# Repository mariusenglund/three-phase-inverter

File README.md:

# 3-phase DC/AC converter with SV-PWM
This repository holds materials of our bachelor's thesis carried out at the Western Norway University of Applied Sciences (HVL), Department of Computer Science, Electrical Engineering and Mathematical Sciences in the spring of 2023.

The thesis can be found at [HVL Open](https://hdl.handle.net/11250/3105460).

> We hope that this report will serve as a valuable resource for those who are interested in the field, and we encourage further development of the provided resources.

## About the Project
The project was aimed at realizing the design and fabrication of a three-phase DC-to-AC converter utilizing the Space Vector Pulse Width Modulation (SV-PWM) algorithm.

<p align="center">
   
   &nbsp; &nbsp; &nbsp; &nbsp;
   
</p>

## Further Work
For suggestions on further work, please refer to the thesis.

## Available Resources
In order to facilitate further advancement, the following resources are made accessible from this repo:

* [PCB design files](pcb-design-files)
* [Source code](source-code)
* [Simulation files](simulation-files)

The repository also contains a [laboratory exercise proposal](/laboratory-exercise/laboratory-exercise-proposal.pdf) that makes use of the inverter. It is worth noting that this exercise is presented in Norwegian.

## License
The resources provided in this repository are released under the GNU General Public License. See the [LICENSE](LICENSE) file for more information.

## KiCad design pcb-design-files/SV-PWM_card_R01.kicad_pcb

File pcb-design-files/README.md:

## PCB Design Files
Download the KiCad project from this location.

***Be aware that the files are still a work in progress.***

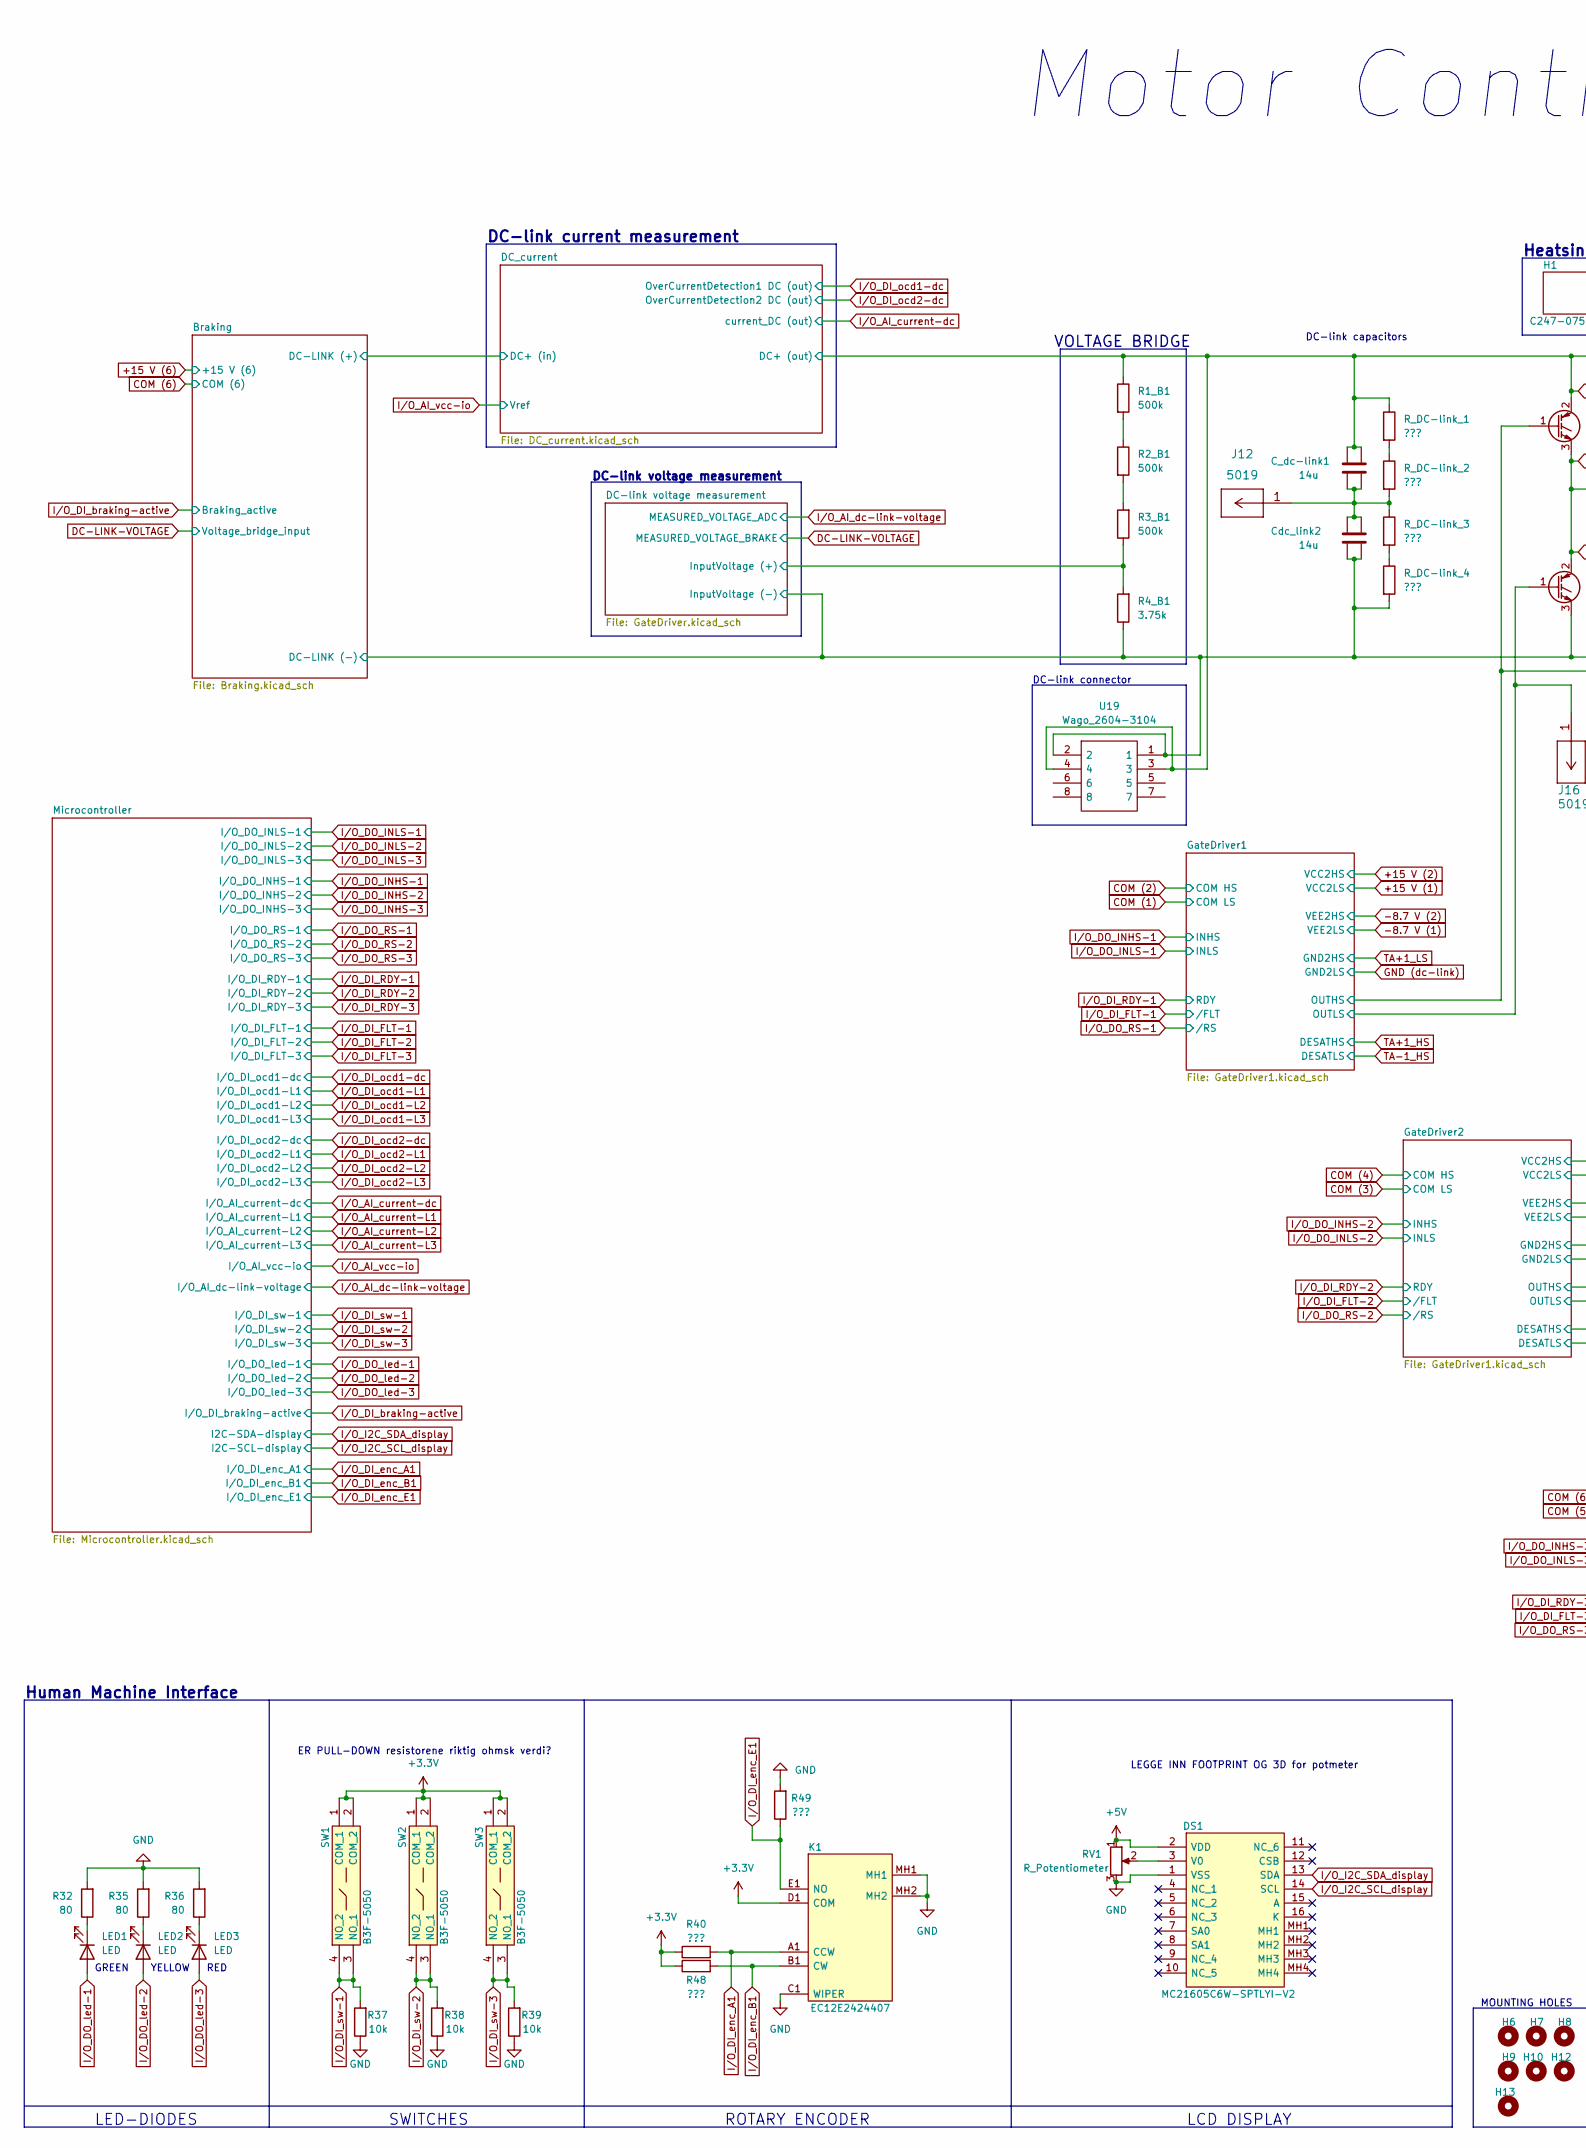
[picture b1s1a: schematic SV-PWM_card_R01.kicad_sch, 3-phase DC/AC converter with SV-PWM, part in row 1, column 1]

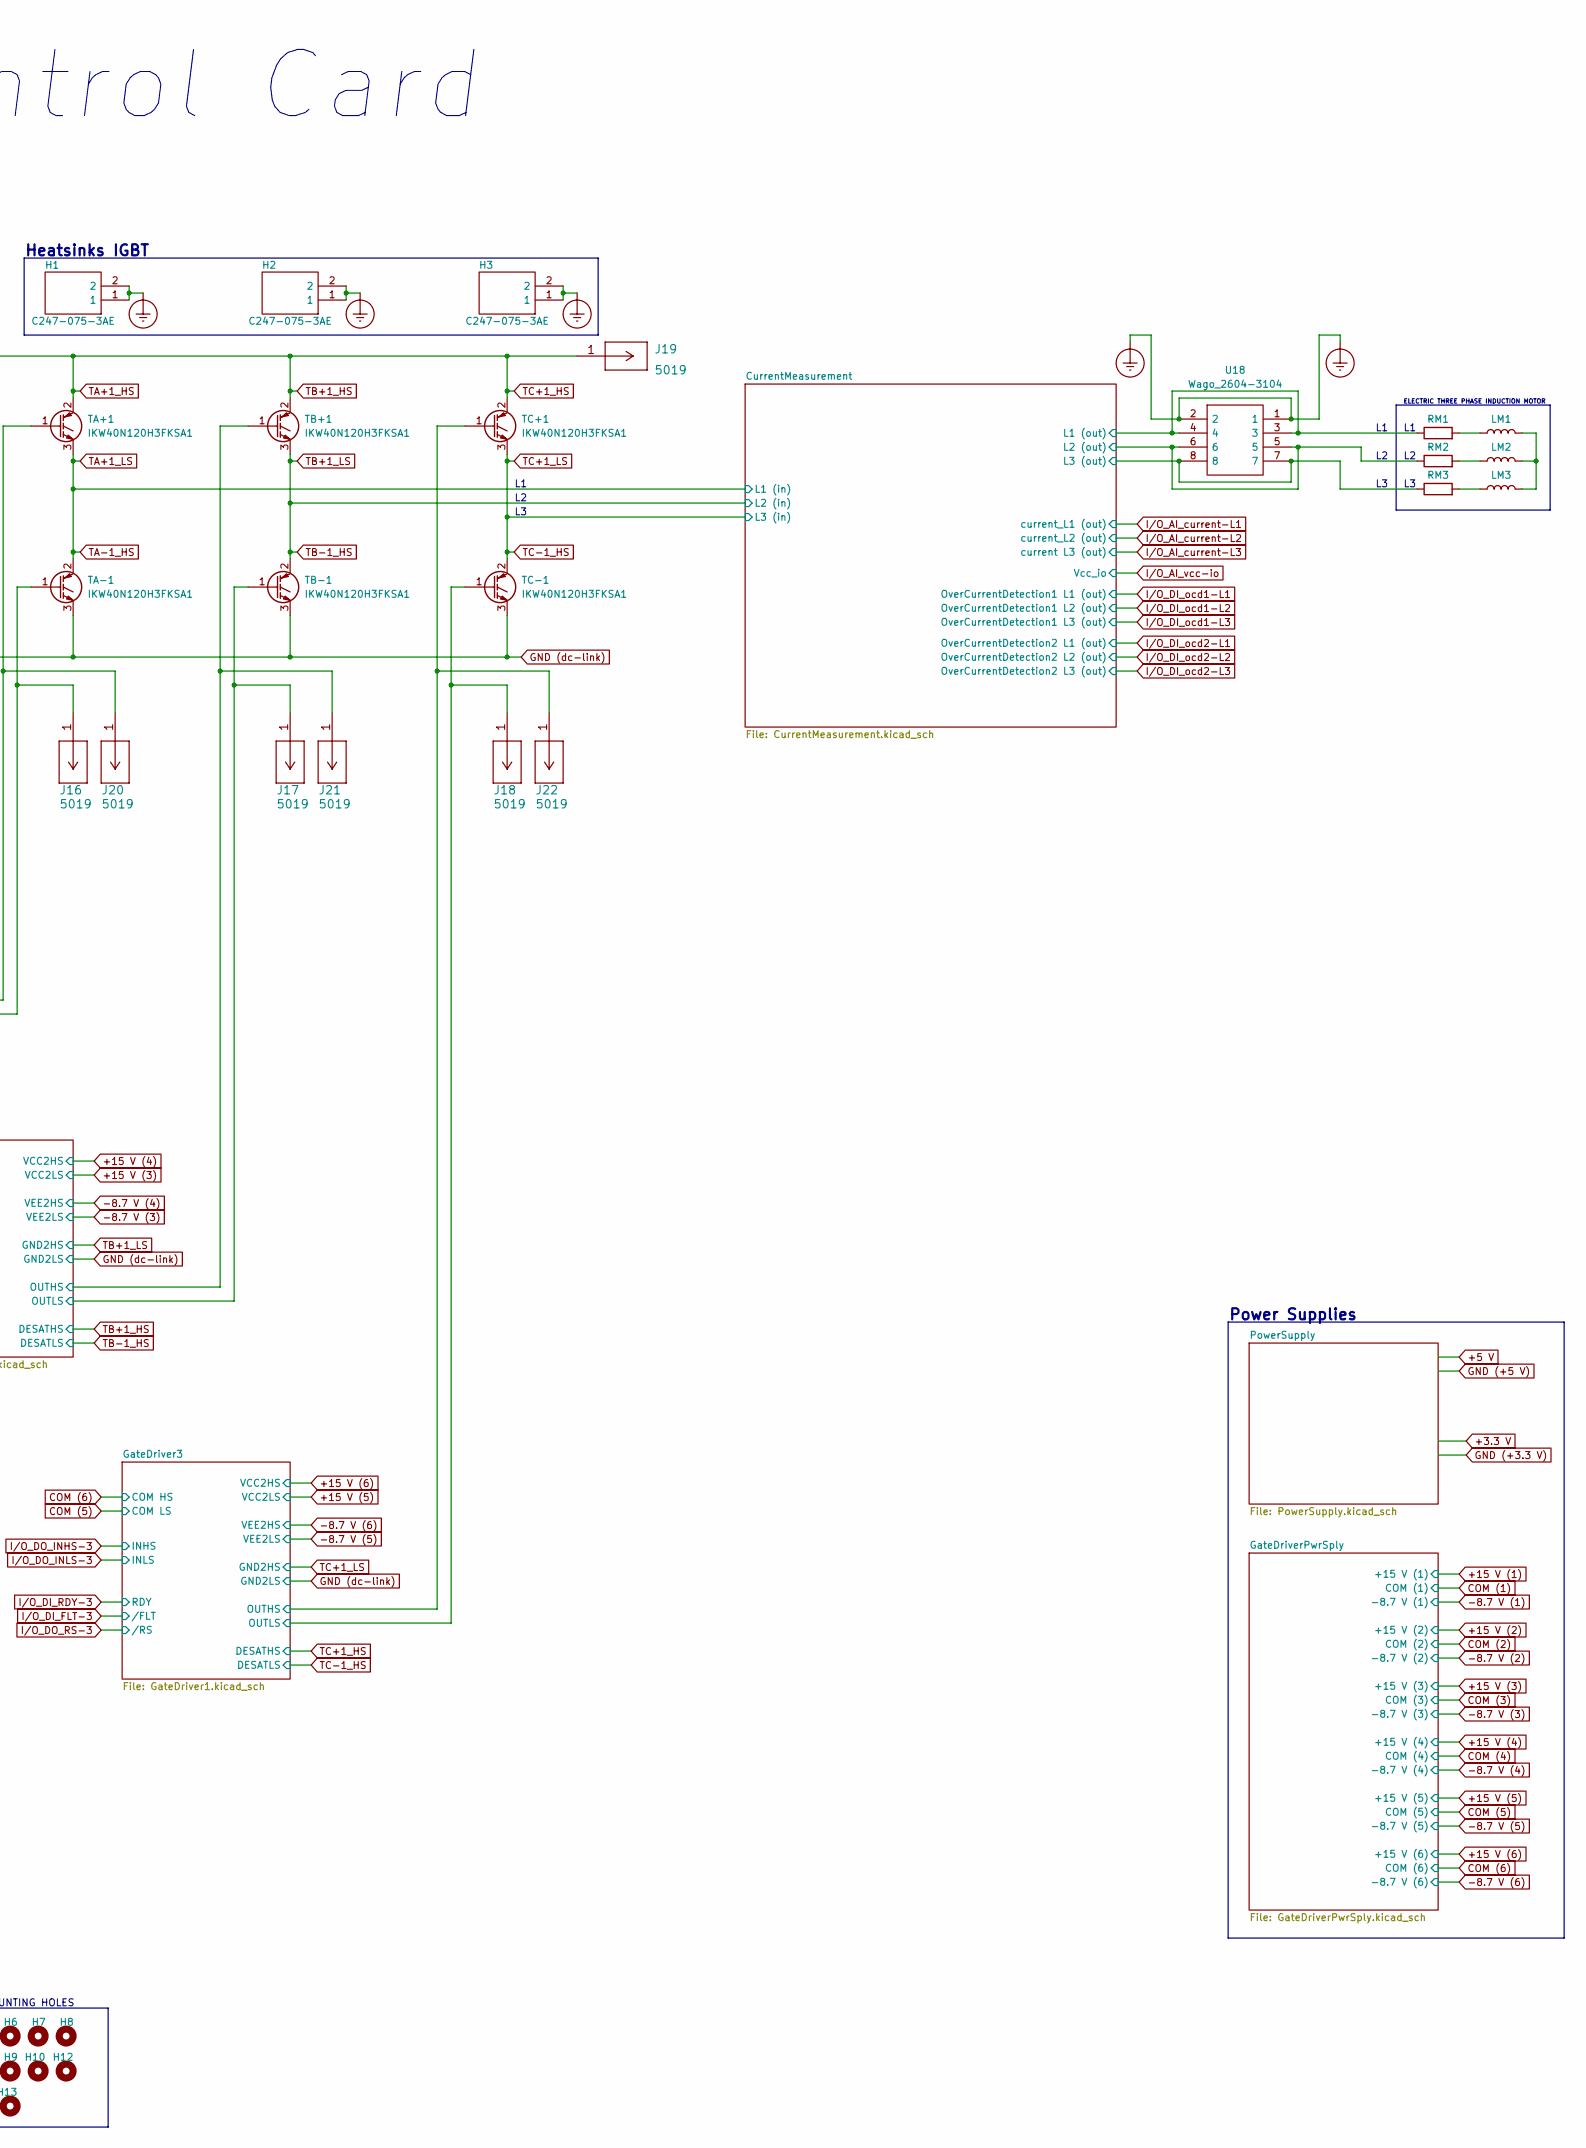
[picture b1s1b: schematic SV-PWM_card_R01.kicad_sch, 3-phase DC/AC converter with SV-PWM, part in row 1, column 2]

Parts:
C_dc-link1: 14u; DC-link-capacitor-B32776G0146K000
Cdc_link2: 14u; DC-link-capacitor-B32776G0146K000
DS1: MC21605C6W-SPTLYI-V2; Display_MC21605C6WSPTLYIV2; Manufacturer_Part_Number MC21605C6W-SPTLYI-V2
H1, H2, H3: C247-075-3AE; Heatsink_C2470753AE; Manufacturer_Part_Number C247-075-3AE; Mouser Part Number 588-C247-075-3AE
H6, H7, H8, H9, H10, H12, H13: MountingHole; MountingHole_4.3mm_M4_DIN965_Pad
J12, J16, J17, J18, J19, J20, J21, J22: 5019; Keystone-5019
K1: EC12E2424407; Encoder_EC12E2424407; Manufacturer_Part_Number EC12E2424407; Mouser Part Number 688-EC12E2424407
LED1: LED; LED_green
LED2: LED; LED_yellow
LED3: LED; LED_red
LM1, LM2, LM3: L
R1_B1, R2_B1, R3_B1: 500k; R_1206_3216Metric_Pad1.30x1.75mm_HandSolder
R4_B1: 3.75k; R_1206_3216Metric_Pad1.30x1.75mm_HandSolder
R32, R35, R36: 80; R_1206_3216Metric_Pad1.30x1.75mm_HandSolder
R37, R38, R39: 10k; R_1206_3216Metric_Pad1.30x1.75mm_HandSolder
R40, R48, R49: ???; R_1206_3216Metric_Pad1.30x1.75mm_HandSolder
RM1, RM2, RM3: R
RV1: R_Potentiometer; Potmeter_3386F1203TLF
R_DC-link_1, R_DC-link_2, R_DC-link_3, R_DC-link_4: ???; R_1206_3216Metric_Pad1.30x1.75mm_HandSolder
SW1, SW2, SW3: B3F-5050; B3F-4055; Manufacturer_Part_Number B3F-5050; Mouser Part Number 653-B3F-5050
TA+1: IKW40N120H3FKSA1; IGBT-TO544P521X1592X2557-3P
TA-1: IKW40N120H3FKSA1; IGBT-TO544P521X1592X2557-3P
TB+1: IKW40N120H3FKSA1; IGBT-TO544P521X1592X2557-3P
TB-1: IKW40N120H3FKSA1; IGBT-TO544P521X1592X2557-3P
TC+1: IKW40N120H3FKSA1; IGBT-TO544P521X1592X2557-3P
TC-1: IKW40N120H3FKSA1; IGBT-TO544P521X1592X2557-3P
U18, U19: Wago_2604-3104; WAGO-26043104; Manufacturer_Part_Number 2604-3104

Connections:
+3.3V: K1.D1 (COM), R40.1, R48.1, SW1.1 (COM_1), SW1.2 (COM_2), SW2.1 (COM_1), SW2.2 (COM_2), SW3.1 (COM_1), SW3.2 (COM_2); also elsewhere on the board
+5V: DS1.2 (VDD), RV1.1; also elsewhere on the board
/CurrentMeasurement/L1 (out): RM1.1, U18.3, U18.4; also elsewhere on the board
/CurrentMeasurement/L2 (out): RM2.1, U18.5, U18.6; also elsewhere on the board
/CurrentMeasurement/L3 (out): RM3.1, U18.7, U18.8; also elsewhere on the board
/GateDriver1/OUTHS: J20.1, TA+1.1 (G); also elsewhere on the board
/GateDriver1/OUTLS: J16.1, TA-1.1 (G); also elsewhere on the board
/GateDriver2/OUTHS: J21.1, TB+1.1 (G); also elsewhere on the board
/GateDriver2/OUTLS: J17.1, TB-1.1 (G); also elsewhere on the board
/GateDriver3/OUTHS: J22.1, TC+1.1 (G); also elsewhere on the board
/GateDriver3/OUTLS: J18.1, TC-1.1 (G); also elsewhere on the board
COM (2): TA+1.3 (E), TA-1.2 (C); also elsewhere on the board
COM (4): TB+1.3 (E), TB-1.2 (C); also elsewhere on the board
COM (6): TC+1.3 (E), TC-1.2 (C); also elsewhere on the board
DC-LINK-VOLTAGE: R3_B1.1, R4_B1.2; also elsewhere on the board
Earth_Protective: H1.1, H1.2, H2.1, H2.2, H3.1, H3.2, U18.1, U18.2; also elsewhere on the board
GND: DS1.1 (VSS), K1.C1 (WIPER), K1.MH1, K1.MH2, R32.2, R35.2, R36.2, R37.1, R38.1, R39.1, R49.2, RV1.3; also elsewhere on the board
GND (dc-link): Cdc_link2.2, Cdc_link2.4, R4_B1.1, R_DC-link_4.2, TA-1.3 (E), TB-1.3 (E), TC-1.3 (E), U19.1, U19.2; also elsewhere on the board
I/O_DI_enc_A1: K1.A1 (CCW), R40.2; also elsewhere on the board
I/O_DI_enc_B1: K1.B1 (CW), R48.2; also elsewhere on the board
I/O_DI_enc_E1: K1.E1 (NO), R49.1; also elsewhere on the board
I/O_DI_sw-1: R37.2, SW1.3 (NO_1), SW1.4 (NO_2); also elsewhere on the board
I/O_DI_sw-2: R38.2, SW2.3 (NO_1), SW2.4 (NO_2); also elsewhere on the board
I/O_DI_sw-3: R39.2, SW3.3 (NO_1), SW3.4 (NO_2); also elsewhere on the board
I/O_DO_led-1: LED1.2 (A); also elsewhere on the board
I/O_DO_led-2: LED2.2 (A); also elsewhere on the board
I/O_DO_led-3: LED3.2 (A); also elsewhere on the board
I/O_I2C_SCL_display: DS1.14 (SCL); also elsewhere on the board
I/O_I2C_SDA_display: DS1.13 (SDA); also elsewhere on the board
unnamed: C_dc-link1.2, C_dc-link1.4, Cdc_link2.1, Cdc_link2.3, J12.1, R_DC-link_2.2, R_DC-link_3.1
unnamed: DS1.3 (V0), RV1.2
unnamed: LED1.1 (K), R32.1
unnamed: LED2.1 (K), R35.1
unnamed: LED3.1 (K), R36.1
unnamed: LM1.1, RM1.2
unnamed: LM1.2, LM2.2, LM3.2
unnamed: LM2.1, RM2.2
unnamed: LM3.1, RM3.2
unnamed: R1_B1.2, R2_B1.1
unnamed: R2_B1.2, R3_B1.2
unnamed: R_DC-link_1.2, R_DC-link_2.1
unnamed: R_DC-link_3.2, R_DC-link_4.1
TA+1_HS: C_dc-link1.1, C_dc-link1.3, J19.1, R1_B1.1, R_DC-link_1.1, TA+1.2 (C), TB+1.2 (C), TC+1.2 (C), U19.3, U19.4; also elsewhere on the board

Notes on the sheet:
DC-link capacitors
DC-link connector
DC-link current measurement
LCD DISPLAY
LEGGE INN FOOTPRINT OG 3D for potmeter
LED-DIODES
DC-link voltage measurement
Power Supplies
RED
GREEN
Heatsinks IGBT
ER PULL-DOWN resistorene riktig ohmsk verdi?
ROTARY ENCODER
YELLOW
MOUNTING HOLES
SWITCHES
Motor Control Card
VOLTAGE BRIDGE
ELECTRIC THREE PHASE INDUCTION MOTOR
Human Machine Interface

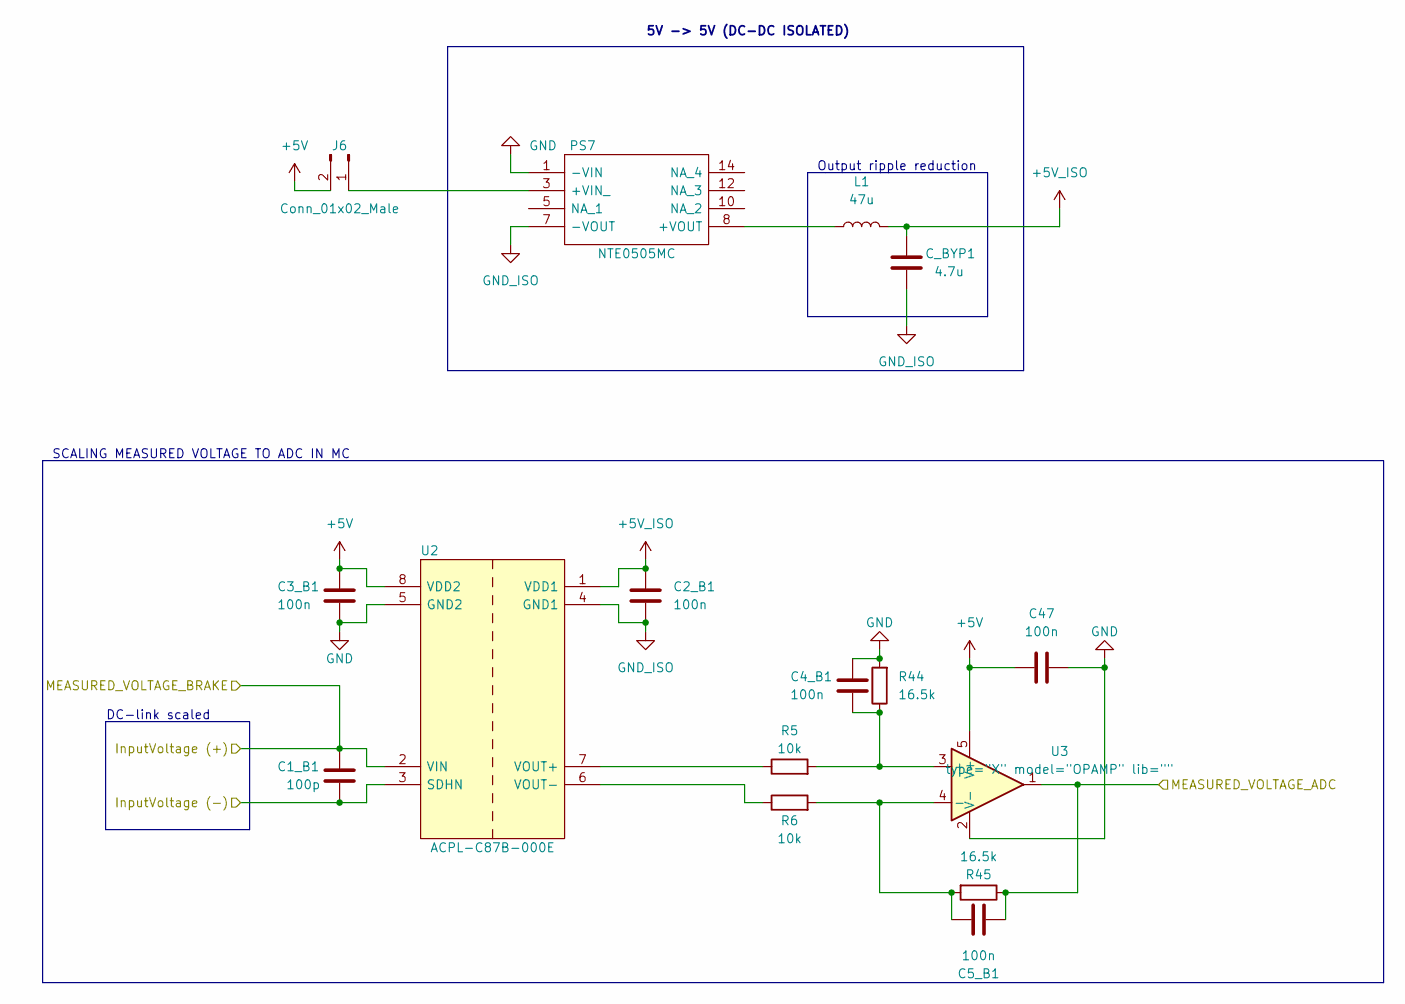
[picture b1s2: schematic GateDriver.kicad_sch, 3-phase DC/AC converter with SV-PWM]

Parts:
C1_B1: 100p; C_1206_3216Metric_Pad1.33x1.80mm_HandSolder
C2_B1, C3_B1, C4_B1, C5_B1, C47: 100n; C_1206_3216Metric_Pad1.33x1.80mm_HandSolder
C_BYP1: 4.7u; C_1206_3216Metric_Pad1.33x1.80mm_HandSolder
J6: Conn_01x02_Male; PinHeader_1x02_P1.00mm_Vertical
L1: 47u; L_2010_5025Metric_Pad1.52x2.65mm_HandSolder
PS7: NTE0505MC; DC-DC-NTE0505MC; Manufacturer_Part_Number NTE0505MC; Mouser Part Number 580-NTE0505MC
R5, R6: 10k; R_1206_3216Metric_Pad1.30x1.75mm_HandSolder
R44, R45: 16.5k; R_1206_3216Metric_Pad1.30x1.75mm_HandSolder
U2: ACPL-C87B-000E; ACPL-SOIC127P1150X331-8N; Manufacturer_Part_Number ACPL-C87B-000E; Mouser Part Number 630-ACPL-C87B-000E
U3: type="X" model="OPAMP" lib=""; OPA237-SOT95P280X145-5N

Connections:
+5V: C3_B1.1, C47.1, J6.2, U2.8 (VDD2), U3.5 (V+); also elsewhere on the board
+5V_ISO: C2_B1.1, C_BYP1.1, L1.2, U2.1 (VDD1)
DC-LINK-VOLTAGE: C1_B1.1, U2.2 (VIN); also elsewhere on the board
GND: C3_B1.2, C4_B1.2, C47.2, PS7.1 (-VIN), R44.2, U2.5 (GND2), U3.2 (V-); also elsewhere on the board
GND (dc-link): C1_B1.2, U2.3 (SDHN); also elsewhere on the board
GND_ISO: C2_B1.2, C_BYP1.2, PS7.7 (-VOUT), U2.4 (GND1)
I/O_AI_dc-link-voltage: C5_B1.1, R45.1, U3.1; also elsewhere on the board
unnamed: C4_B1.1, R5.2, R44.1, U3.3 (+)
unnamed: C5_B1.2, R6.2, R45.2, U3.4 (-)
unnamed: J6.1, PS7.3 (+VIN_)
unnamed: L1.1, PS7.8 (+VOUT)
unnamed: R5.1, U2.7 (VOUT+)
unnamed: R6.1, U2.6 (VOUT-)

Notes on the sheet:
DC-link scaled
Output ripple reduction
SCALING MEASURED VOLTAGE TO ADC IN MC
5V -> 5V (DC-DC ISOLATED)

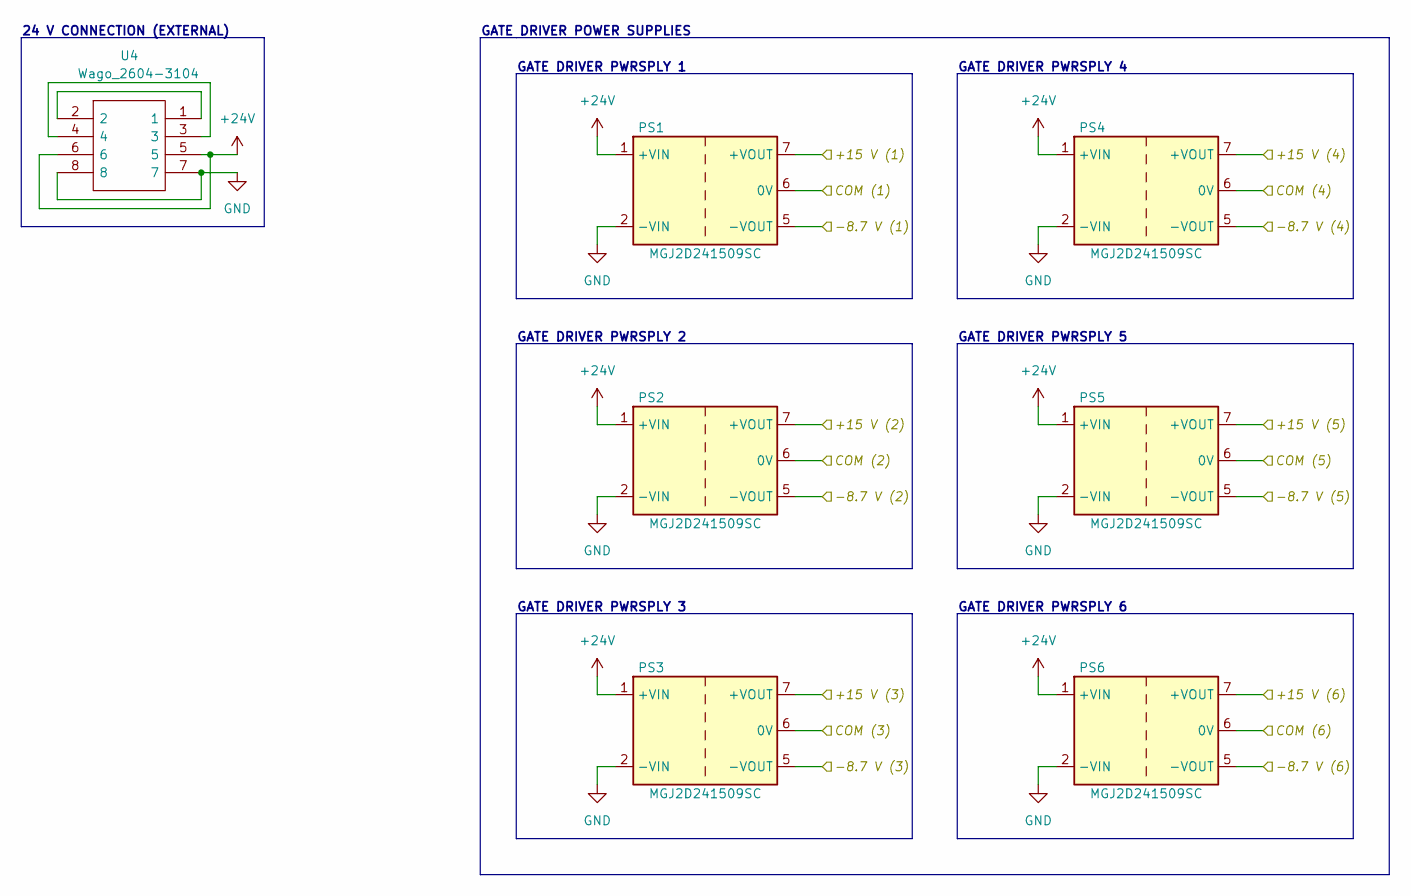
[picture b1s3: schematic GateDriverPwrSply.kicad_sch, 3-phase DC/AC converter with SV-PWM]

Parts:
PS1, PS2, PS3, PS4, PS5, PS6: MGJ2D241509SC; Converter_DCDC_Murata_MGJ2DxxxxxxSC_THT
U4: Wago_2604-3104; WAGO-26043104; Manufacturer_Part_Number 2604-3104

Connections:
+15 V (1): PS1.7 (+VOUT); also elsewhere on the board
+15 V (2): PS2.7 (+VOUT); also elsewhere on the board
+15 V (3): PS3.7 (+VOUT); also elsewhere on the board
+15 V (4): PS4.7 (+VOUT); also elsewhere on the board
+15 V (5): PS5.7 (+VOUT); also elsewhere on the board
+15 V (6): PS6.7 (+VOUT); also elsewhere on the board
+24V: PS1.1 (+VIN), PS2.1 (+VIN), PS3.1 (+VIN), PS4.1 (+VIN), PS5.1 (+VIN), PS6.1 (+VIN), U4.5, U4.6; also elsewhere on the board
-8.7 V (1): PS1.5 (-VOUT); also elsewhere on the board
-8.7 V (2): PS2.5 (-VOUT); also elsewhere on the board
-8.7 V (3): PS3.5 (-VOUT); also elsewhere on the board
-8.7 V (4): PS4.5 (-VOUT); also elsewhere on the board
-8.7 V (5): PS5.5 (-VOUT); also elsewhere on the board
-8.7 V (6): PS6.5 (-VOUT); also elsewhere on the board
COM (2): PS2.6 (0V); also elsewhere on the board
COM (4): PS4.6 (0V); also elsewhere on the board
COM (6): PS6.6 (0V); also elsewhere on the board
GND: PS1.2 (-VIN), PS2.2 (-VIN), PS3.2 (-VIN), PS4.2 (-VIN), PS5.2 (-VIN), PS6.2 (-VIN), U4.7, U4.8; also elsewhere on the board
GND (dc-link): PS1.6 (0V), PS3.6 (0V), PS5.6 (0V); also elsewhere on the board
unnamed: U4.1, U4.2
unnamed: U4.3, U4.4

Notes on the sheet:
GATE DRIVER PWRSPLY 6
GATE DRIVER PWRSPLY 5
GATE DRIVER POWER SUPPLIES
GATE DRIVER PWRSPLY 4
GATE DRIVER PWRSPLY 2
24 V CONNECTION (EXTERNAL)
GATE DRIVER PWRSPLY 3
GATE DRIVER PWRSPLY 1

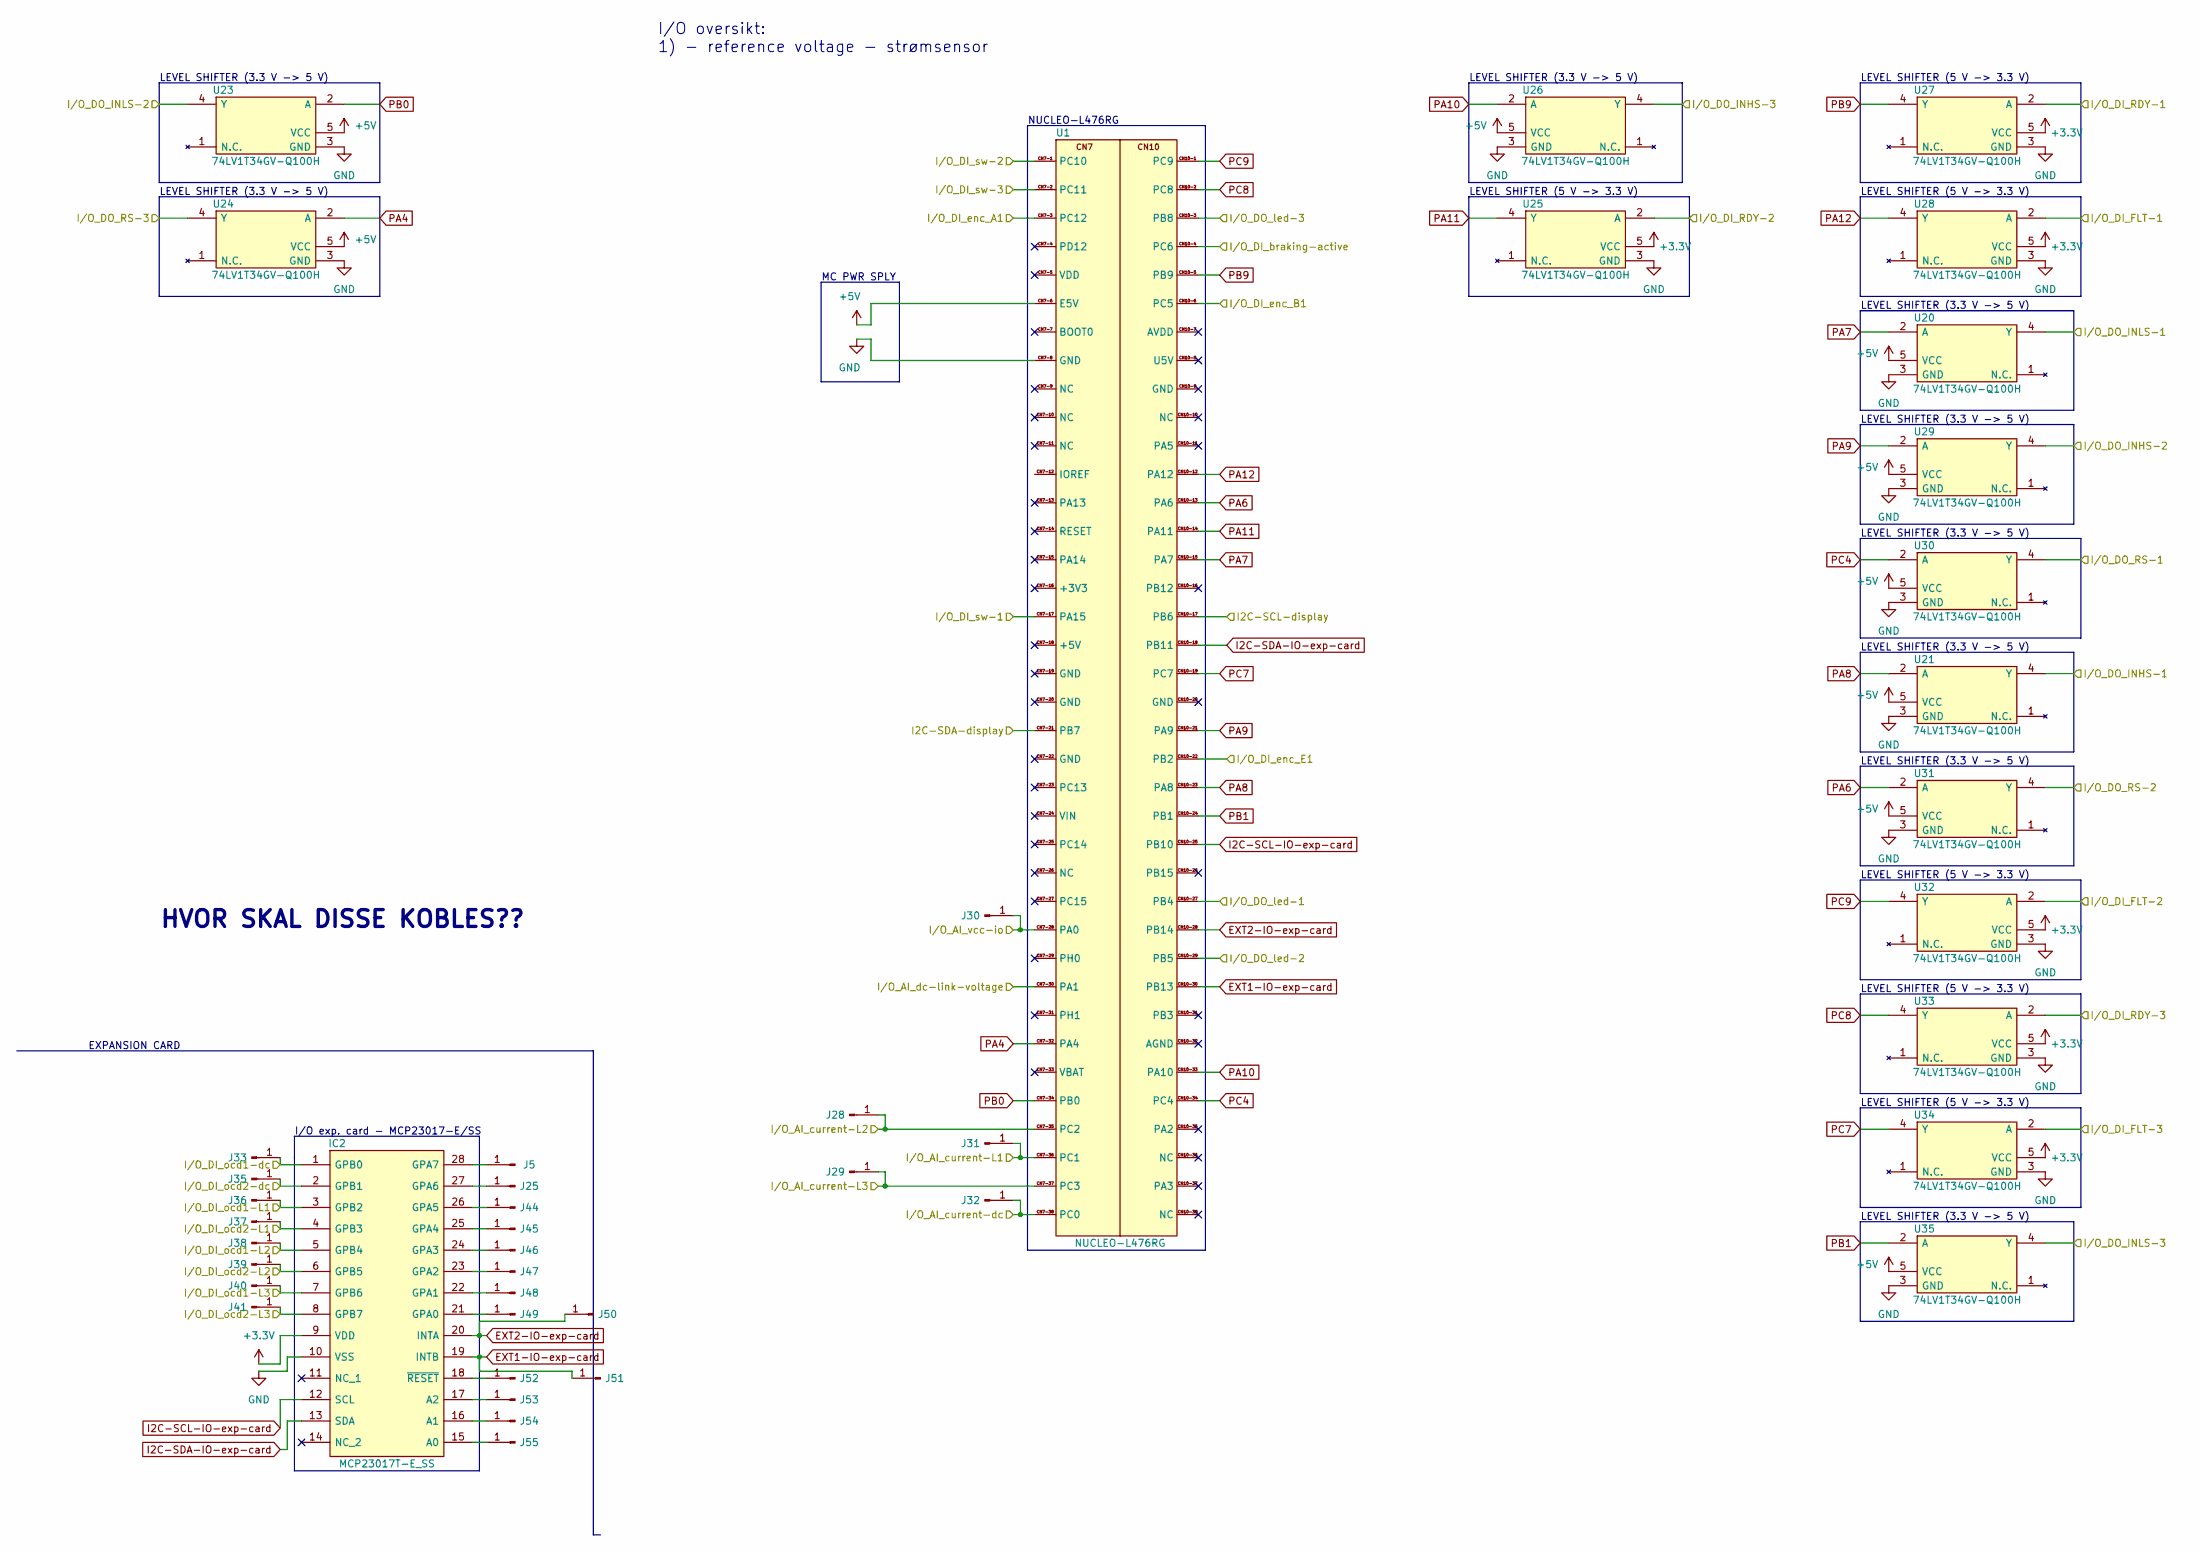
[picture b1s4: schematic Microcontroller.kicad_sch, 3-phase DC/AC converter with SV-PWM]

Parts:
IC2: MCP23017T-E_SS; MCP23017T-ESS-SOP65P780X200-28N; Manufacturer_Part_Number MCP23017T-E/SS; Mouser Part Number 579-MCP23017T-E/SS
J5, J25, J28, J29, J30, J31, J32, J33, J35, J36, J37, J38, J39, J40, J41, J44, J45, J46, J47, J48, J49, J50, J51, J52, J53, J54, J55: Conn_01x01_Male; PinHeader_1x01_P1.00mm_Vertical
U1: NUCLEO-L476RG; PCB-receptable Nucleo-L476RG
U20, U21, U23, U24, U25, U26, U27, U28, U29, U30, U31, U32, U33, U34, U35: 74LV1T34GV-Q100H; nexperia-SOT95P275X110-5N; Manufacturer_Part_Number 74LV1T34GV-Q100H; Mouser Part Number 771-74LV1T34GV-Q100H

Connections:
+3.3V: IC2.9 (VDD), U25.5 (VCC), U27.5 (VCC), U28.5 (VCC), U32.5 (VCC), U33.5 (VCC), U34.5 (VCC); also elsewhere on the board
+5V: U1.CN7-6 (E5V), U20.5 (VCC), U21.5 (VCC), U23.5 (VCC), U24.5 (VCC), U26.5 (VCC), U29.5 (VCC), U30.5 (VCC), U31.5 (VCC), U35.5 (VCC); also elsewhere on the board
EXT1-IO-exp-card: IC2.19 (INTB), J51.1, U1.CN10-30 (PB13)
EXT2-IO-exp-card: IC2.20 (INTA), J50.1, U1.CN10-28 (PB14)
GND: IC2.10 (VSS), U1.CN7-8 (GND), U20.3 (GND), U21.3 (GND), U23.3 (GND), U24.3 (GND), U25.3 (GND), U26.3 (GND), U27.3 (GND), U28.3 (GND), U29.3 (GND), U30.3 (GND), U31.3 (GND), U32.3 (GND), U33.3 (GND), U34.3 (GND), U35.3 (GND); also elsewhere on the board
I2C-SCL-IO-exp-card: IC2.12 (SCL), U1.CN10-25 (PB10)
I2C-SDA-IO-exp-card: IC2.13 (SDA), U1.CN10-18 (PB11)
I/O_AI_current-L1: J31.1, U1.CN7-36 (PC1); also elsewhere on the board
I/O_AI_current-L2: J28.1, U1.CN7-35 (PC2); also elsewhere on the board
I/O_AI_current-L3: J29.1, U1.CN7-37 (PC3); also elsewhere on the board
I/O_AI_current-dc: J32.1, U1.CN7-38 (PC0); also elsewhere on the board
I/O_AI_dc-link-voltage: U1.CN7-30 (PA1); also elsewhere on the board
I/O_AI_vcc-io: J30.1, U1.CN7-28 (PA0); also elsewhere on the board
I/O_DI_FLT-1: U28.2 (A); also elsewhere on the board
I/O_DI_FLT-2: U32.2 (A); also elsewhere on the board
I/O_DI_FLT-3: U34.2 (A); also elsewhere on the board
I/O_DI_RDY-1: U27.2 (A); also elsewhere on the board
I/O_DI_RDY-2: U25.2 (A); also elsewhere on the board
I/O_DI_RDY-3: U33.2 (A); also elsewhere on the board
I/O_DI_braking-active: U1.CN10-4 (PC6); also elsewhere on the board
I/O_DI_enc_A1: U1.CN7-3 (PC12); also elsewhere on the board
I/O_DI_enc_B1: U1.CN10-6 (PC5); also elsewhere on the board
I/O_DI_enc_E1: U1.CN10-22 (PB2); also elsewhere on the board
I/O_DI_ocd1-L1: IC2.3 (GPB2), J36.1; also elsewhere on the board
I/O_DI_ocd1-L2: IC2.5 (GPB4), J38.1; also elsewhere on the board
I/O_DI_ocd1-L3: IC2.7 (GPB6), J40.1; also elsewhere on the board
I/O_DI_ocd1-dc: IC2.1 (GPB0), J33.1; also elsewhere on the board
I/O_DI_ocd2-L1: IC2.4 (GPB3), J37.1; also elsewhere on the board
I/O_DI_ocd2-L2: IC2.6 (GPB5), J39.1; also elsewhere on the board
I/O_DI_ocd2-L3: IC2.8 (GPB7), J41.1; also elsewhere on the board
I/O_DI_ocd2-dc: IC2.2 (GPB1), J35.1; also elsewhere on the board
I/O_DI_sw-1: U1.CN7-17 (PA15); also elsewhere on the board
I/O_DI_sw-2: U1.CN7-1 (PC10); also elsewhere on the board
I/O_DI_sw-3: U1.CN7-2 (PC11); also elsewhere on the board
I/O_DO_INHS-1: U21.4 (Y); also elsewhere on the board
I/O_DO_INHS-2: U29.4 (Y); also elsewhere on the board
I/O_DO_INHS-3: U26.4 (Y); also elsewhere on the board
I/O_DO_INLS-1: U20.4 (Y); also elsewhere on the board
I/O_DO_INLS-2: U23.4 (Y); also elsewhere on the board
I/O_DO_INLS-3: U35.4 (Y); also elsewhere on the board
I/O_DO_RS-1: U30.4 (Y); also elsewhere on the board
I/O_DO_RS-2: U31.4 (Y); also elsewhere on the board
I/O_DO_RS-3: U24.4 (Y); also elsewhere on the board
I/O_DO_led-1: U1.CN10-27 (PB4); also elsewhere on the board
I/O_DO_led-2: U1.CN10-29 (PB5); also elsewhere on the board
I/O_DO_led-3: U1.CN10-3 (PB8); also elsewhere on the board
I/O_I2C_SCL_display: U1.CN10-17 (PB6); also elsewhere on the board
I/O_I2C_SDA_display: U1.CN7-21 (PB7); also elsewhere on the board
unnamed: IC2.15 (A0), J55.1
unnamed: IC2.16 (A1), J54.1
unnamed: IC2.17 (A2), J53.1
unnamed: IC2.18 (~RESET), J52.1
unnamed: IC2.21 (GPA0), J49.1
unnamed: IC2.22 (GPA1), J48.1
unnamed: IC2.23 (GPA2), J47.1
unnamed: IC2.24 (GPA3), J46.1
unnamed: IC2.25 (GPA4), J45.1
unnamed: IC2.26 (GPA5), J44.1
unnamed: IC2.27 (GPA6), J25.1
unnamed: IC2.28 (GPA7), J5.1
PA4: U1.CN7-32 (PA4), U24.2 (A)
PA6: U1.CN10-13 (PA6), U31.2 (A)
PA7: U1.CN10-15 (PA7), U20.2 (A)
PA8: U1.CN10-23 (PA8), U21.2 (A)
PA9: U1.CN10-21 (PA9), U29.2 (A)
PA10: U1.CN10-33 (PA10), U26.2 (A)
PA11: U1.CN10-14 (PA11), U25.4 (Y)
PA12: U1.CN10-12 (PA12), U28.4 (Y)
PB0: U1.CN7-34 (PB0), U23.2 (A)
PB1: U1.CN10-24 (PB1), U35.2 (A)
PB9: U1.CN10-5 (PB9), U27.4 (Y)
PC4: U1.CN10-34 (PC4), U30.2 (A)
PC7: U1.CN10-19 (PC7), U34.4 (Y)
PC8: U1.CN10-2 (PC8), U33.4 (Y)
PC9: U1.CN10-1 (PC9), U32.4 (Y)

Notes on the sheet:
LEVEL SHIFTER (3.3 V -> 5 V)
NUCLEO-L476RG
LEVEL SHIFTER (5 V -> 3.3 V)
HVOR SKAL DISSE KOBLES??
MC PWR SPLY
I/O exp. card - MCP23017-E/SS
EXPANSION CARD
I/O oversikt: 1) - reference voltage - strømsensor

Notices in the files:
parts and their libraries:
Copyright 2021 Accelerated Designs. All rights reserved.
